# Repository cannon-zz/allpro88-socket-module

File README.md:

# KiCad Model of Logical Devices' ALLPRO88 PLCC Socket Module

## Overview

This provides a KiCad [schematic](https://github.com/user-attachments/files/24761395/socket_module_plcc_schematic.pdf) of the PLCC socket module for use with Logic Devices' ALLPRO88 software-driven device programmer.  The service manual scans available on the internet are incomprehensible.  I believe the schematic is correct.  The PCB's size and the locations of the DIN connectors, 48 pin ZIF connector and decoupling capacitors and transistors all match the original.  All other part locations are approximate, the PCB has not been routed, and the footprints for the PLCC sockets are not correct.  The PLCC sockets here have the wrong hole pattern, and are mirrored with respect to the originals.  The original module used Yamaichi IC120 series sockets, the "dead bug" variants (for which the chips are inserted upside down).  See a datasheet for the correct hole patterns.  The objective is not to allow a PLCC socket module to be reproduced from this project, but to provide a starting point for making a custom socket module.

## Board Size

Measuring my PCB to the nearest 0.5 mm, the PCB is 25.70 cm x 20.45 cm.

If it's imperial, and we allow some +/- for the saw cut accuracy, it could be 10 1/8" x 8" (= 25.7175 cm x 20.32 cm).

I found a comment in the service manual that the PCB is 10.100" x 8.05x" (x is unreadable, could be 0, 6 or 8 maybe).  0.001" = 0.0254 mm, so I don't think it really matters if that digit is a 0 or an 8.  10.1" x 8.05" = 25.65 cm x 20.45 cm which is within 0.5 mm of my measurements.

## DIN Connector Placement

From the corner of the PCB closest to the 44 pin PLCC socket, I mesaure pin C32 of J1 to be 100.8 mm horizontally from that corner, and 67.2 mm vertically.  The two DIN connectors appear to be positioned with respect to each other on a 2.54 mm grid:  A1 to A1 is 18 * 2.54 mm = 45.72 mm.  The status LEDs and their resistors appear to be on a 2.54 mm grid, centred between the DIN connectors

I suggest plugging the DIN connectors into the base, then placing the PCB onto them and either tightening the screws to hold them in that position or soldering enough pins to secure them, then removing the PCB with the connectors to continue soldering.  That way they're guaranteed to be aligned with their sockets after being soldered into position.

## Signal Names

The scans available on the internet of the original schematic, both for the socket module and the programmer's mother board, are incomprehensible.  Also, there are several inconsistent channel numbering schemes in Logical Devices' original documentation.  So:  what's here is my own invention.  Make of it what you will.

 * GND:  system power supply return.
 * -8 V, -5 V, +5 V, +12V, VREF:  main system power supplies.
 * VADJ:  main programmable, high current, power supply.  All pin driver voltages are derived from this.
 * VSR, VTH, VPU, ILIN:  pin driver power supplies.
 * !SOCKETEN:  active-low device select line indicating that the address bus is in the range 0x0280 to 0x02ff inclusively.  This is a 128 byte window reserved for the socket module.  On the universal PLCC module, reading from any address in this range returns the socket module ID, while writing to addresses in this range control the registers used to switch the pin decoupling capacitors on and off.
 * \phi_{0}, \phi_{1}:  the two phases used for driving the TTL clock output modes of the pin drivers.  When they are active they are guaranteed to be 180 degrees out of phase, but they can become inactive and enter the same state.
 * !XFER:  active low line to clock the pin driver DACs
 * !RD, !WR:  active low read- and write-enable signals.
 * !LED_BUSY, LED_IDLE:  common collector drives for the busy (red) and idle (green) LEDs.
 * !RESET:  active low system reset.  On the PLCC module, resets the decoupling capacitor registers to 0 (capacitors disconnected).
 * !SELECT0 -- !SELECT4:  active low device select lines for the first 5 pin driver modules, corresponding to channels 0 through 39 inclusively.  The ALLPRO88 was preceded by an earlier product that had only 40 channels, and it was presumably thought to be handy to have these signals brought out to the socket module to avoid duplicating address decoding circuitry in the event that lots of complex pin driver circuitry was needed for some part.
 * A0 -- A9:  partial system address bus.  The system address bus is 12 bits, but only the low 10 are present on the socket module.  Together with !SOCKETEN, only A0--A6 are needed to address the 128 byte window reserved for the socket module.
 * D0 -- D7:  system data bus.
 * OUT0 -- OUT87:  the 88 pin driver inputs/outputs.
 * SPARE1:  unused signal line that connects to the socket module, all pin driver boards, and both analogue 1 and analogue 2.  There are two unused voltage DACs on analogue 2, and I think a sensible thing to do would be to jumper one of them to this in line, to provide an additional programmable voltage to the system.  For example, the fixed 5 V linear regulators that generate the "TTL" output voltage on the pin driver boards could be replaced with adjustable regulators programmed by this voltage, making it easier to support non- 5 V logic.

## PAL

The PAL device is a look-up table for chip select line decoding.  To (I assume) simplify trace routing, pin driver channels are connected to ZIF socket pins close to their location on the DIN connector, in groups of 8 with 4 on one side of the socket and 4 on the other, while decoupling capacitor transistor drivers are connected to transistors sequentially along each side of the socket.  Additionally, for (again I assume) historical reasons only the first 40 channels have sequential addresses, the final 8 are offset at slightly higher addresses.  Altogther, these conditions create a somewhat complex relationship between the numerical address on the address bus and which transistor on which FET chip should be turned on or off, which motivates the use of a programmable logic device.

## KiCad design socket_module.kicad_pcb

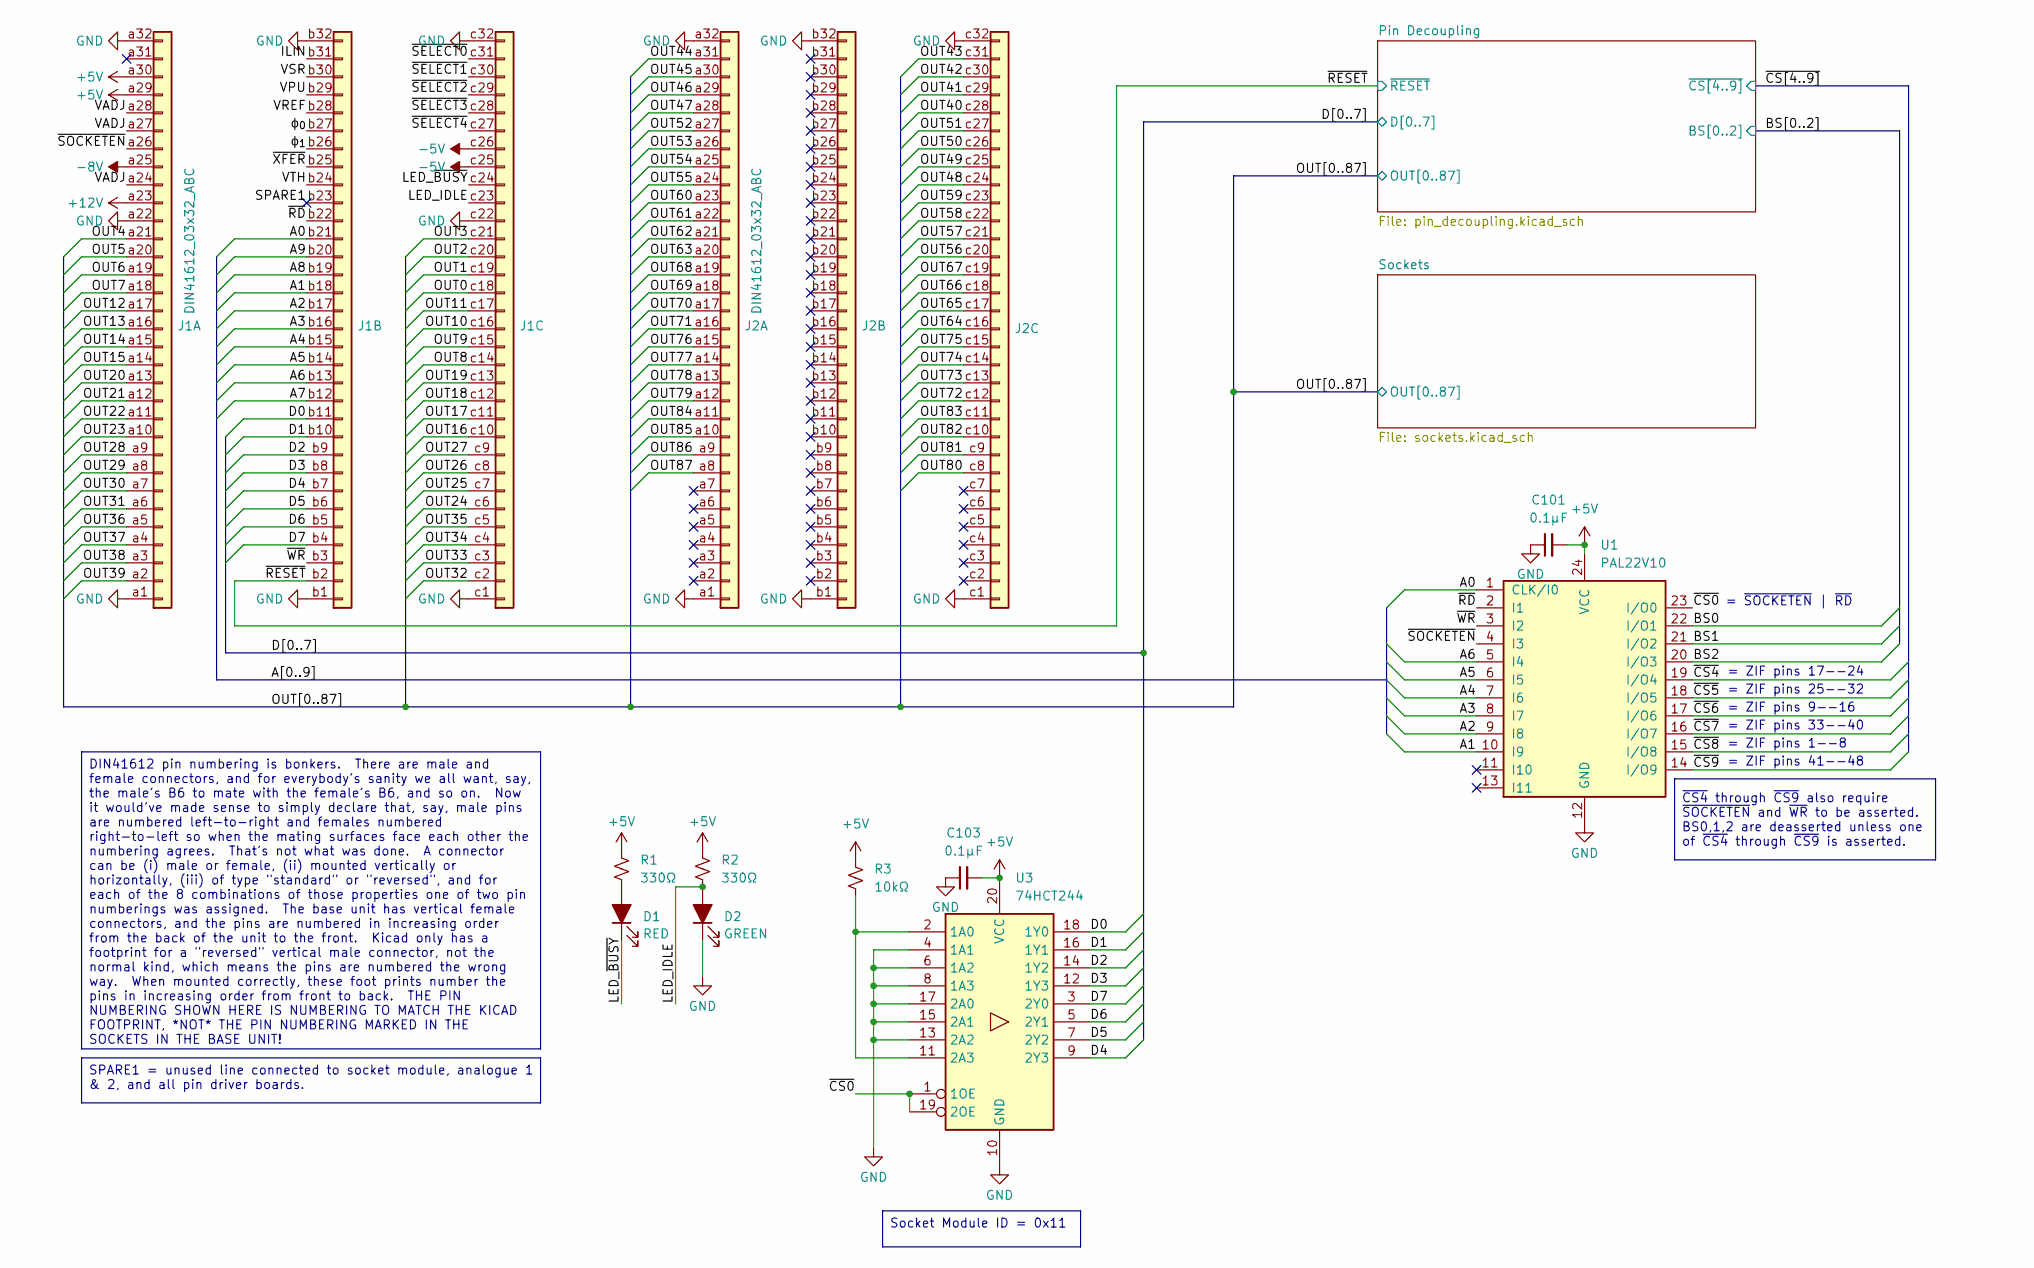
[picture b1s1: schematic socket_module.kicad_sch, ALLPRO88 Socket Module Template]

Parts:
C101, C103: 0.1μF; C_Disc_D7.5mm_W2.5mm_P5.00mm
D1: RED; LED_Rectangular_W5.0mm_H2.0mm
D2: GREEN; LED_Rectangular_W5.0mm_H2.0mm
J1, J2: DIN41612_03x32_ABC; DIN41612_R_3x32_Male_Vertical_THT
R1, R2: 330Ω; R_Axial_DIN0207_L6.3mm_D2.5mm_P10.16mm_Horizontal
R3: 10kΩ; R_Axial_DIN0207_L6.3mm_D2.5mm_P10.16mm_Horizontal
U1: PAL22V10; DIP-24_W7.62mm_Socket_LongPads
U3: 74HCT244; DIP-20_W7.62mm_LongPads

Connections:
+5V: C101.2, C103.2, J1.a29, J1.a30, R1.1, R2.1, R3.1, U1.24 (VCC), U3.20 (VCC); also elsewhere on the board
+12V: J1.a23
-5V: J1.c25, J1.c26
-8V: J1.a25
/A0: J1.b21, U1.1 (CLK/I0)
/A1: J1.b18, U1.10 (I9)
/A2: J1.b17, U1.9 (I8)
/A3: J1.b16, U1.8 (I7)
/A4: J1.b15, U1.7 (I6)
/A5: J1.b14, U1.6 (I5)
/A6: J1.b13, U1.5 (I4)
/A7: J1.b12
/A8: J1.b19
/A9: J1.b20
/BS0: U1.22 (I/O1); also elsewhere on the board
/BS1: U1.21 (I/O2); also elsewhere on the board
/BS2: U1.20 (I/O3); also elsewhere on the board
/D0: J1.b11, U3.18 (1Y0); also elsewhere on the board
/D1: J1.b10, U3.16 (1Y1)
/D2: J1.b9, U3.14 (1Y2)
/D3: J1.b8, U3.12 (1Y3)
/D4: J1.b7, U3.9 (2Y3)
/D5: J1.b6, U3.7 (2Y2)
/D6: J1.b5, U3.5 (2Y1)
/D7: J1.b4, U3.3 (2Y0)
/ILIN: J1.b31
/LED_IDLE: D2.2 (A), J1.c23, R2.2
/LED_~BUSY: D1.1 (K), J1.c24
/OUT0: J1.c18; also elsewhere on the board
/OUT1: J1.c19; also elsewhere on the board
/OUT2: J1.c20; also elsewhere on the board
/OUT3: J1.c21; also elsewhere on the board
/OUT4: J1.a21; also elsewhere on the board
/OUT5: J1.a20; also elsewhere on the board
/OUT6: J1.a19; also elsewhere on the board
/OUT7: J1.a18; also elsewhere on the board
/OUT8: J1.c14; also elsewhere on the board
/OUT9: J1.c15; also elsewhere on the board
/OUT10: J1.c16; also elsewhere on the board
/OUT11: J1.c17; also elsewhere on the board
/OUT12: J1.a17; also elsewhere on the board
/OUT13: J1.a16; also elsewhere on the board
/OUT14: J1.a15; also elsewhere on the board
/OUT15: J1.a14; also elsewhere on the board
/OUT16: J1.c10; also elsewhere on the board
/OUT17: J1.c11; also elsewhere on the board
/OUT18: J1.c12; also elsewhere on the board
/OUT19: J1.c13; also elsewhere on the board
/OUT20: J1.a13; also elsewhere on the board
/OUT21: J1.a12; also elsewhere on the board
/OUT22: J1.a11; also elsewhere on the board
/OUT23: J1.a10; also elsewhere on the board
/OUT24: J1.c6; also elsewhere on the board
/OUT25: J1.c7; also elsewhere on the board
/OUT26: J1.c8; also elsewhere on the board
/OUT27: J1.c9; also elsewhere on the board
/OUT28: J1.a9; also elsewhere on the board
/OUT29: J1.a8; also elsewhere on the board
/OUT30: J1.a7; also elsewhere on the board
/OUT31: J1.a6; also elsewhere on the board
/OUT32: J1.c2; also elsewhere on the board
/OUT33: J1.c3; also elsewhere on the board
/OUT34: J1.c4; also elsewhere on the board
/OUT35: J1.c5; also elsewhere on the board
/OUT36: J1.a5; also elsewhere on the board
/OUT37: J1.a4; also elsewhere on the board
/OUT38: J1.a3; also elsewhere on the board
/OUT39: J1.a2; also elsewhere on the board
/OUT40: J2.c28; also elsewhere on the board
/OUT41: J2.c29; also elsewhere on the board
/OUT42: J2.c30; also elsewhere on the board
/OUT43: J2.c31; also elsewhere on the board
/OUT44: J2.a31; also elsewhere on the board
/OUT45: J2.a30; also elsewhere on the board
/OUT46: J2.a29; also elsewhere on the board
/OUT47: J2.a28; also elsewhere on the board
/OUT48: J2.c24; also elsewhere on the board
/OUT49: J2.c25; also elsewhere on the board
/OUT50: J2.c26; also elsewhere on the board
/OUT51: J2.c27; also elsewhere on the board
/OUT52: J2.a27; also elsewhere on the board
/OUT53: J2.a26; also elsewhere on the board
/OUT54: J2.a25; also elsewhere on the board
/OUT55: J2.a24; also elsewhere on the board
/OUT56: J2.c20; also elsewhere on the board
/OUT57: J2.c21; also elsewhere on the board
/OUT58: J2.c22; also elsewhere on the board
/OUT59: J2.c23; also elsewhere on the board
/OUT60: J2.a23; also elsewhere on the board
/OUT61: J2.a22; also elsewhere on the board
/OUT62: J2.a21; also elsewhere on the board
/OUT63: J2.a20; also elsewhere on the board
/OUT64: J2.c16; also elsewhere on the board
/OUT65: J2.c17; also elsewhere on the board
/OUT66: J2.c18; also elsewhere on the board
/OUT67: J2.c19; also elsewhere on the board
/OUT68: J2.a19; also elsewhere on the board
/OUT69: J2.a18; also elsewhere on the board
/OUT70: J2.a17; also elsewhere on the board
/OUT71: J2.a16; also elsewhere on the board
/OUT72: J2.c12; also elsewhere on the board
/OUT73: J2.c13; also elsewhere on the board
/OUT74: J2.c14; also elsewhere on the board
/OUT75: J2.c15; also elsewhere on the board
/OUT76: J2.a15; also elsewhere on the board
/OUT77: J2.a14; also elsewhere on the board
/OUT78: J2.a13; also elsewhere on the board
/OUT79: J2.a12; also elsewhere on the board
/OUT80: J2.c8
/OUT81: J2.c9
/OUT82: J2.c10; also elsewhere on the board
/OUT83: J2.c11; also elsewhere on the board
/OUT84: J2.a11; also elsewhere on the board
/OUT85: J2.a10; also elsewhere on the board
/OUT86: J2.a9
/OUT87: J2.a8
/SPARE1: J1.b23
/VADJ: J1.a24, J1.a27, J1.a28
/VPU: J1.b29
/VREF: J1.b28
/VSR: J1.b30
/VTH: J1.b24 (Pin_a24)
/~CS0: U1.23 (I/O0), U3.1 (1OE), U3.19 (2OE)
/~CS4: U1.19 (I/O4); also elsewhere on the board
/~CS5: U1.18 (I/O5); also elsewhere on the board
/~CS6: U1.17 (I/O6); also elsewhere on the board
/~CS7: U1.16 (I/O7); also elsewhere on the board
/~CS8: U1.15 (I/O8); also elsewhere on the board
/~CS9: U1.14 (I/O9); also elsewhere on the board
/~RD: J1.b22, U1.2 (I1)
/~RESET: J1.b2; also elsewhere on the board
/~SELECT0: J1.c31
/~SELECT1: J1.c30
/~SELECT2: J1.c29
/~SELECT3: J1.c28
/~SELECT4: J1.c27
/~SOCKETEN: J1.a26, U1.4 (I3)
/~WR: J1.b3, U1.3 (I2)
/~XFER: J1.b25
/ϕ_{0}: J1.b27
/ϕ_{1}: J1.b26
GND: C101.1, C103.1, D2.1 (K), J1.a1, J1.a22, J1.a32, J1.b1, J1.b32, J1.c1, J1.c22, J1.c32, J2.a1, J2.a32, J2.b1, J2.b32, J2.c1, J2.c32, U1.12 (GND), U3.4 (1A1), U3.6 (1A2), U3.8 (1A3), U3.10 (GND), U3.13 (2A2), U3.15 (2A1), U3.17 (2A0); also elsewhere on the board
unnamed: D1.2 (A), R1.2
unnamed: R3.2, U3.2 (1A0), U3.11 (2A3)

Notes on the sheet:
= ZIF pins 33--40
= ~{SOCKETEN} | ~{RD}
= ZIF pins 17--24
= ZIF pins 41--48
= ZIF pins 1--8
= ZIF pins 25--32
= ZIF pins 9--16
~{CS4} through ~{CS9} also require ~{SOCKETEN} and ~{WR} to be asserted. BS0,1,2 are deasserted unless one of ~{CS4} through ~{CS9} is asserted.
Socket Module ID = 0x11
DIN41612 pin numbering is bonkers. There are male and female connectors, and for everybody's sanity we all want, say, the male's B6 to mate with the female's B6, and so on. Now it would've made sense to simply declare that, say, male pins are numbered left-to-right and females numbered right-to-lef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
SPARE1 = unused line connected to socket module, analogue 1 & 2, and all pin driver boards.

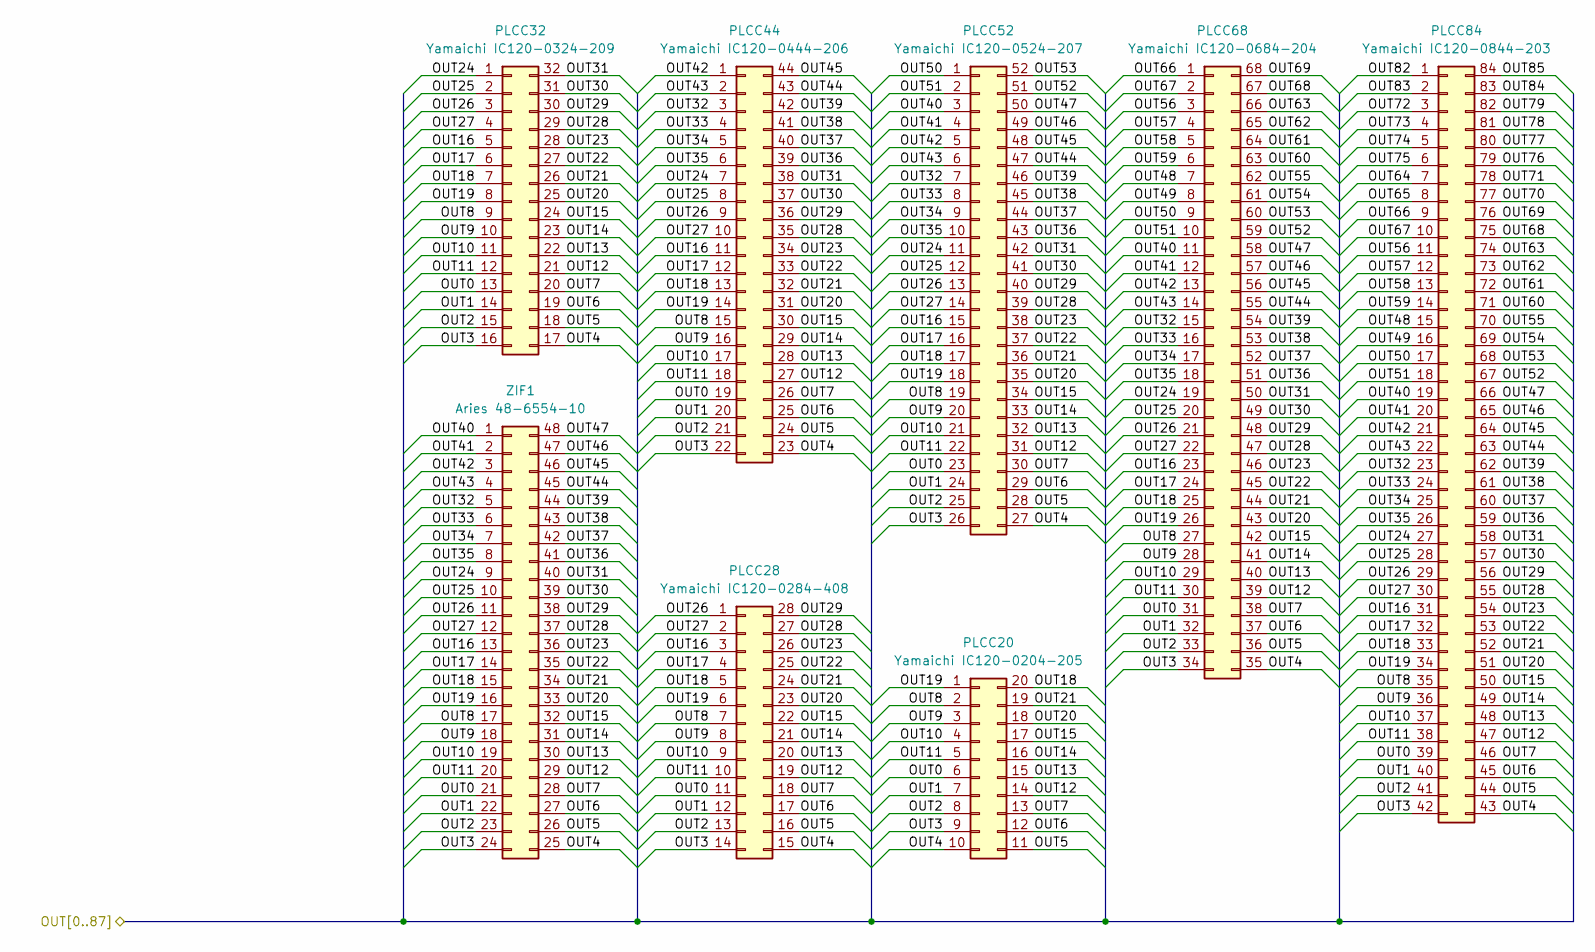
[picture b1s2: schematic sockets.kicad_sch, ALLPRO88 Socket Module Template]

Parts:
PLCC20: Yamaichi IC120-0204-205; PLCC-20_THT-Socket
PLCC28: Yamaichi IC120-0284-408; PLCC-28_THT-Socket
PLCC32: Yamaichi IC120-0324-209; PLCC-32_THT-Socket
PLCC44: Yamaichi IC120-0444-206; PLCC-44_THT-Socket
PLCC52: Yamaichi IC120-0524-207; PLCC-52_THT-Socket
PLCC68: Yamaichi IC120-0684-204; PLCC-68_THT-Socket
PLCC84: Yamaichi IC120-0844-203; PLCC-84_THT-Socket
ZIF1: Aries 48-6554-10; DIP-48_W15.24mm_Socket_LongPads

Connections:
/OUT0: PLCC20.6, PLCC28.11, PLCC32.13, PLCC44.19, PLCC52.23, PLCC68.31, PLCC84.39, ZIF1.21; also elsewhere on the board
/OUT1: PLCC20.7, PLCC28.12, PLCC32.14, PLCC44.20, PLCC52.24, PLCC68.32, PLCC84.40, ZIF1.22; also elsewhere on the board
/OUT2: PLCC20.8, PLCC28.13, PLCC32.15, PLCC44.21, PLCC52.25, PLCC68.33, PLCC84.41, ZIF1.23; also elsewhere on the board
/OUT3: PLCC20.9, PLCC28.14, PLCC32.16, PLCC44.22, PLCC52.26, PLCC68.34, PLCC84.42, ZIF1.24; also elsewhere on the board
/OUT4: PLCC20.10, PLCC28.15, PLCC32.17, PLCC44.23, PLCC52.27, PLCC68.35, PLCC84.43, ZIF1.25; also elsewhere on the board
/OUT5: PLCC20.11, PLCC28.16, PLCC32.18, PLCC44.24, PLCC52.28, PLCC68.36, PLCC84.44, ZIF1.26; also elsewhere on the board
/OUT6: PLCC20.12, PLCC28.17, PLCC32.19, PLCC44.25, PLCC52.29, PLCC68.37, PLCC84.45, ZIF1.27; also elsewhere on the board
/OUT7: PLCC20.13, PLCC28.18, PLCC32.20, PLCC44.26, PLCC52.30, PLCC68.38, PLCC84.46, ZIF1.28; also elsewhere on the board
/OUT8: PLCC20.2, PLCC28.7, PLCC32.9, PLCC44.15, PLCC52.19, PLCC68.27, PLCC84.35, ZIF1.17; also elsewhere on the board
/OUT9: PLCC20.3, PLCC28.8, PLCC32.10, PLCC44.16, PLCC52.20, PLCC68.28, PLCC84.36, ZIF1.18; also elsewhere on the board
/OUT10: PLCC20.4, PLCC28.9, PLCC32.11, PLCC44.17, PLCC52.21, PLCC68.29, PLCC84.37, ZIF1.19; also elsewhere on the board
/OUT11: PLCC20.5, PLCC28.10, PLCC32.12, PLCC44.18, PLCC52.22, PLCC68.30, PLCC84.38, ZIF1.20; also elsewhere on the board
/OUT12: PLCC20.14, PLCC28.19, PLCC32.21, PLCC44.27, PLCC52.31, PLCC68.39, PLCC84.47, ZIF1.29; also elsewhere on the board
/OUT13: PLCC20.15, PLCC28.20, PLCC32.22, PLCC44.28, PLCC52.32, PLCC68.40, PLCC84.48, ZIF1.30; also elsewhere on the board
/OUT14: PLCC20.16, PLCC28.21, PLCC32.23, PLCC44.29, PLCC52.33, PLCC68.41, PLCC84.49, ZIF1.31; also elsewhere on the board
/OUT15: PLCC20.17, PLCC28.22, PLCC32.24, PLCC44.30, PLCC52.34, PLCC68.42, PLCC84.50, ZIF1.32; also elsewhere on the board
/OUT16: PLCC28.3, PLCC32.5, PLCC44.11, PLCC52.15, PLCC68.23, PLCC84.31, ZIF1.13; also elsewhere on the board
/OUT17: PLCC28.4, PLCC32.6, PLCC44.12, PLCC52.16, PLCC68.24, PLCC84.32, ZIF1.14; also elsewhere on the board
/OUT18: PLCC20.20, PLCC28.5, PLCC32.7, PLCC44.13, PLCC52.17, PLCC68.25, PLCC84.33, ZIF1.15; also elsewhere on the board
/OUT19: PLCC20.1, PLCC28.6, PLCC32.8, PLCC44.14, PLCC52.18, PLCC68.26, PLCC84.34, ZIF1.16; also elsewhere on the board
/OUT20: PLCC20.18, PLCC28.23, PLCC32.25, PLCC44.31, PLCC52.35, PLCC68.43, PLCC84.51, ZIF1.33; also elsewhere on the board
/OUT21: PLCC20.19, PLCC28.24, PLCC32.26, PLCC44.32, PLCC52.36, PLCC68.44, PLCC84.52, ZIF1.34; also elsewhere on the board
/OUT22: PLCC28.25, PLCC32.27, PLCC44.33, PLCC52.37, PLCC68.45, PLCC84.53, ZIF1.35; also elsewhere on the board
/OUT23: PLCC28.26, PLCC32.28, PLCC44.34, PLCC52.38, PLCC68.46, PLCC84.54, ZIF1.36; also elsewhere on the board
/OUT24: PLCC32.1, PLCC44.7, PLCC52.11, PLCC68.19, PLCC84.27, ZIF1.9; also elsewhere on the board
/OUT25: PLCC32.2, PLCC44.8, PLCC52.12, PLCC68.20, PLCC84.28, ZIF1.10; also elsewhere on the board
/OUT26: PLCC28.1, PLCC32.3, PLCC44.9, PLCC52.13, PLCC68.21, PLCC84.29, ZIF1.11; also elsewhere on the board
/OUT27: PLCC28.2, PLCC32.4, PLCC44.10, PLCC52.14, PLCC68.22, PLCC84.30, ZIF1.12; also elsewhere on the board
/OUT28: PLCC28.27, PLCC32.29, PLCC44.35, PLCC52.39, PLCC68.47, PLCC84.55, ZIF1.37; also elsewhere on the board
/OUT29: PLCC28.28, PLCC32.30, PLCC44.36, PLCC52.40, PLCC68.48, PLCC84.56, ZIF1.38; also elsewhere on the board
/OUT30: PLCC32.31, PLCC44.37, PLCC52.41, PLCC68.49, PLCC84.57, ZIF1.39; also elsewhere on the board
/OUT31: PLCC32.32, PLCC44.38, PLCC52.42, PLCC68.50, PLCC84.58, ZIF1.40; also elsewhere on the board
/OUT32: PLCC44.3, PLCC52.7, PLCC68.15, PLCC84.23, ZIF1.5; also elsewhere on the board
/OUT33: PLCC44.4, PLCC52.8, PLCC68.16, PLCC84.24, ZIF1.6; also elsewhere on the board
/OUT34: PLCC44.5, PLCC52.9, PLCC68.17, PLCC84.25, ZIF1.7; also elsewhere on the board
/OUT35: PLCC44.6, PLCC52.10, PLCC68.18, PLCC84.26, ZIF1.8; also elsewhere on the board
/OUT36: PLCC44.39, PLCC52.43, PLCC68.51, PLCC84.59, ZIF1.41; also elsewhere on the board
/OUT37: PLCC44.40, PLCC52.44, PLCC68.52, PLCC84.60, ZIF1.42; also elsewhere on the board
/OUT38: PLCC44.41, PLCC52.45, PLCC68.53, PLCC84.61, ZIF1.43; also elsewhere on the board
/OUT39: PLCC44.42, PLCC52.46, PLCC68.54, PLCC84.62, ZIF1.44; also elsewhere on the board
/OUT40: PLCC52.3, PLCC68.11, PLCC84.19, ZIF1.1; also elsewhere on the board
/OUT41: PLCC52.4, PLCC68.12, PLCC84.20, ZIF1.2; also elsewhere on the board
/OUT42: PLCC44.1, PLCC52.5, PLCC68.13, PLCC84.21, ZIF1.3; also elsewhere on the board
/OUT43: PLCC44.2, PLCC52.6, PLCC68.14, PLCC84.22, ZIF1.4; also elsewhere on the board
/OUT44: PLCC44.43, PLCC52.47, PLCC68.55, PLCC84.63, ZIF1.45; also elsewhere on the board
/OUT45: PLCC44.44, PLCC52.48, PLCC68.56, PLCC84.64, ZIF1.46; also elsewhere on the board
/OUT46: PLCC52.49, PLCC68.57, PLCC84.65, ZIF1.47; also elsewhere on the board
/OUT47: PLCC52.50, PLCC68.58, PLCC84.66, ZIF1.48; also elsewhere on the board
/OUT48: PLCC68.7, PLCC84.15; also elsewhere on the board
/OUT49: PLCC68.8, PLCC84.16; also elsewhere on the board
/OUT50: PLCC52.1, PLCC68.9, PLCC84.17; also elsewhere on the board
/OUT51: PLCC52.2, PLCC68.10, PLCC84.18; also elsewhere on the board
/OUT52: PLCC52.51, PLCC68.59, PLCC84.67; also elsewhere on the board
/OUT53: PLCC52.52, PLCC68.60, PLCC84.68; also elsewhere on the board
/OUT54: PLCC68.61, PLCC84.69; also elsewhere on the board
/OUT55: PLCC68.62, PLCC84.70; also elsewhere on the board
/OUT56: PLCC68.3, PLCC84.11; also elsewhere on the board
/OUT57: PLCC68.4, PLCC84.12; also elsewhere on the board
/OUT58: PLCC68.5, PLCC84.13; also elsewhere on the board
/OUT59: PLCC68.6, PLCC84.14; also elsewhere on the board
/OUT60: PLCC68.63, PLCC84.71; also elsewhere on the board
/OUT61: PLCC68.64, PLCC84.72; also elsewhere on the board
/OUT62: PLCC68.65, PLCC84.73; also elsewhere on the board
/OUT63: PLCC68.66, PLCC84.74; also elsewhere on the board
/OUT64: PLCC84.7; also elsewhere on the board
/OUT65: PLCC84.8; also elsewhere on the board
/OUT66: PLCC68.1, PLCC84.9; also elsewhere on the board
/OUT67: PLCC68.2, PLCC84.10; also elsewhere on the board
/OUT68: PLCC68.67, PLCC84.75; also elsewhere on the board
/OUT69: PLCC68.68, PLCC84.76; also elsewhere on the board
/OUT70: PLCC84.77; also elsewhere on the board
/OUT71: PLCC84.78; also elsewhere on the board
/OUT72: PLCC84.3; also elsewhere on the board
/OUT73: PLCC84.4; also elsewhere on the board
/OUT74: PLCC84.5; also elsewhere on the board
/OUT75: PLCC84.6; also elsewhere on the board
/OUT76: PLCC84.79; also elsewhere on the board
/OUT77: PLCC84.80; also elsewhere on the board
/OUT78: PLCC84.81; also elsewhere on the board
/OUT79: PLCC84.82; also elsewhere on the board
/OUT82: PLCC84.1; also elsewhere on the board
/OUT83: PLCC84.2; also elsewhere on the board
/OUT84: PLCC84.83; also elsewhere on the board
/OUT85: PLCC84.84; also elsewhere on the board

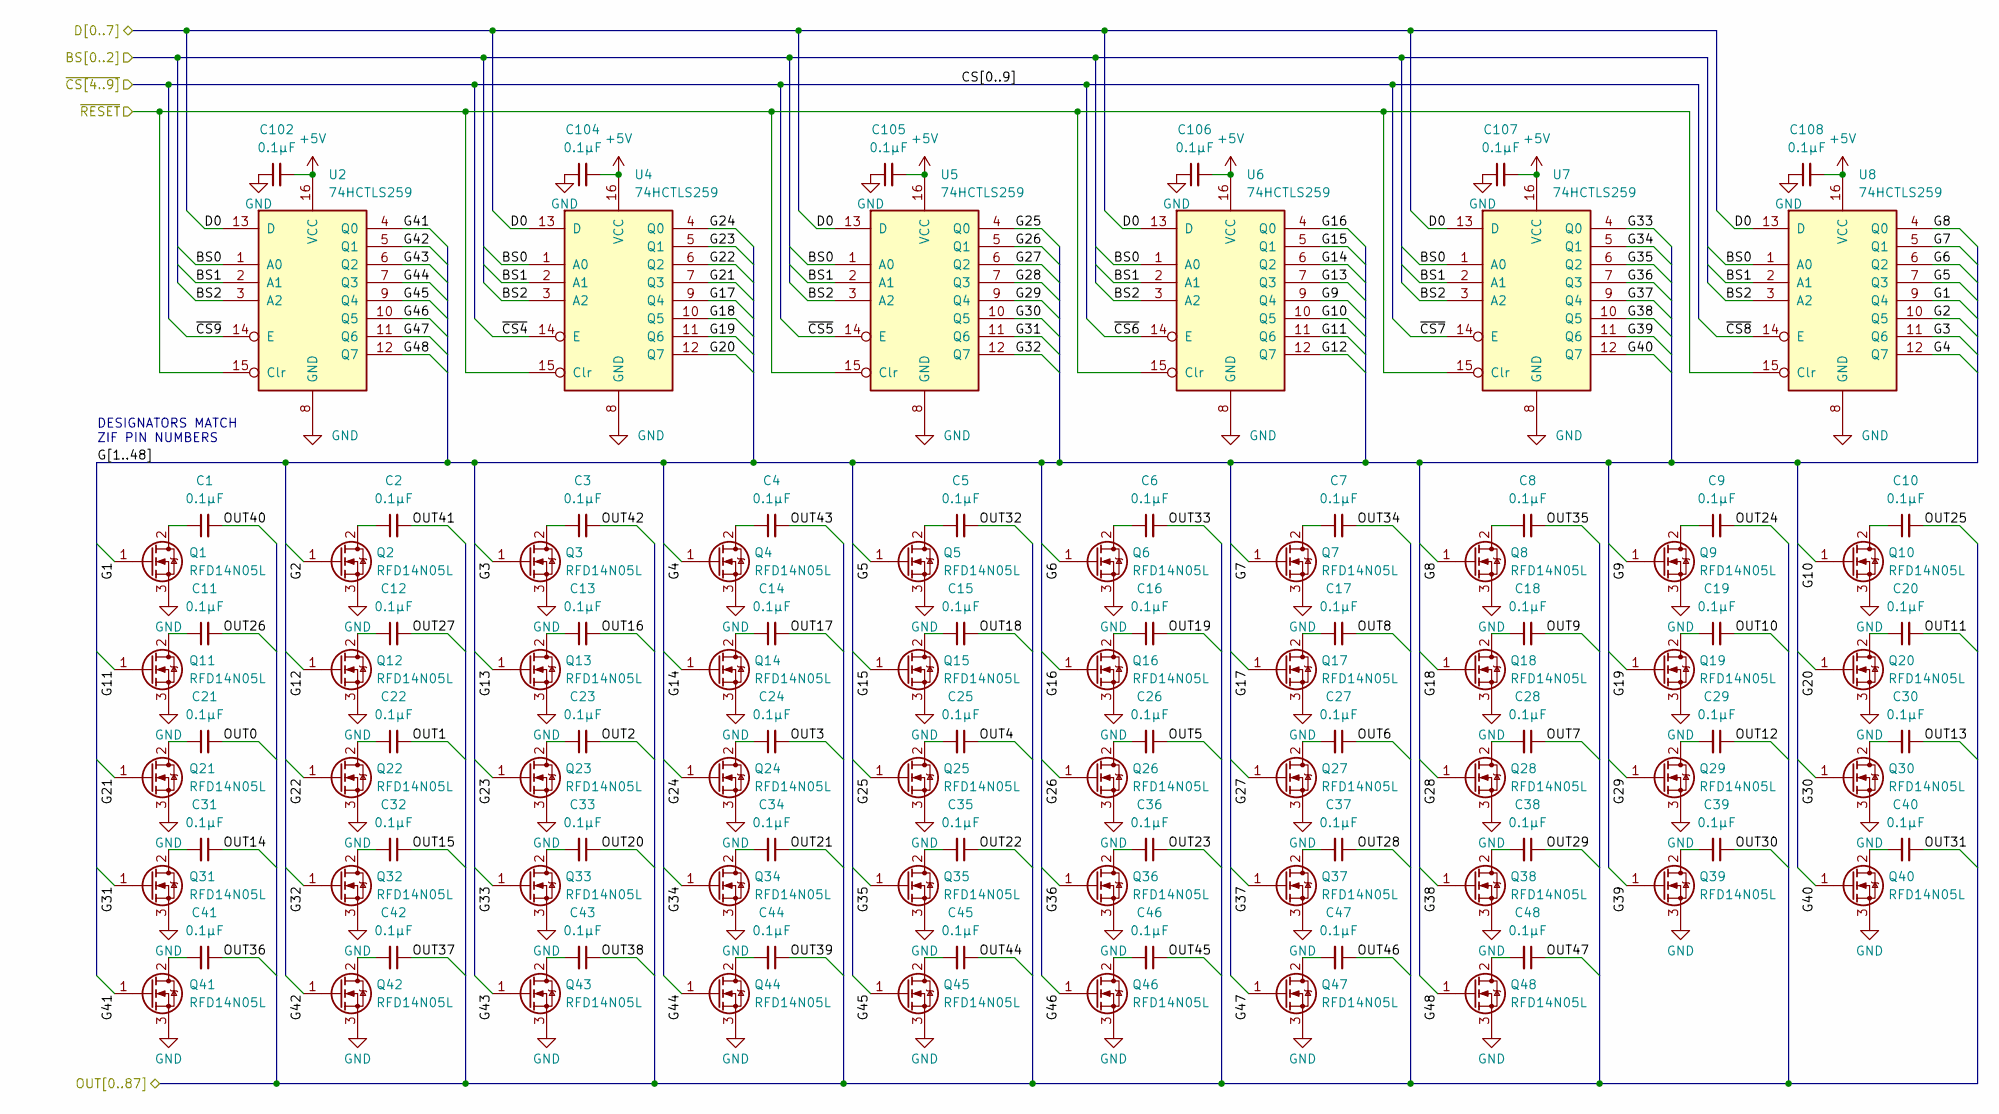
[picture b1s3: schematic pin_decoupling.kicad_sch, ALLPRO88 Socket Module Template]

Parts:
C1, C2, C3, C4, C5, C6, C7, C8, C9, C10, C11, C12, C13, C14, C15, C16, C17, C18, C19, C20, C21, C22, C23, C24, C25, C26, C27, C28, C29, C30, C31, C32, C33, C34, C35, C36, C37, C38, C39, C40, C41, C42, C43, C44, C45, C46, C47, C48, C102, C104, C105, C106, C107, C108: 0.1μF; C_Disc_D7.5mm_W2.5mm_P5.00mm
Q1, Q2, Q3, Q4, Q5, Q6, Q7, Q8, Q9, Q10, Q11, Q12, Q13, Q14, Q15, Q16, Q17, Q18, Q19, Q20, Q21, Q22, Q23, Q24, Q25, Q26, Q27, Q28, Q29, Q30, Q31, Q32, Q33, Q34, Q35, Q36, Q37, Q38, Q39, Q40, Q41, Q42, Q43, Q44, Q45, Q46, Q47, Q48: RFD14N05L; TO-251-3_Vertical
U2, U4, U5, U6, U7, U8: 74HCTLS259; DIP-16_W7.62mm_LongPads

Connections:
+5V: C102.2, C104.2, C105.2, C106.2, C107.2, C108.2, U2.16 (VCC), U4.16 (VCC), U5.16 (VCC), U6.16 (VCC), U7.16 (VCC), U8.16 (VCC); also elsewhere on the board
/BS0: U2.1 (A0), U4.1 (A0), U5.1 (A0), U6.1 (A0), U7.1 (A0), U8.1 (A0); also elsewhere on the board
/BS1: U2.2 (A1), U4.2 (A1), U5.2 (A1), U6.2 (A1), U7.2 (A1), U8.2 (A1); also elsewhere on the board
/BS2: U2.3 (A2), U4.3 (A2), U5.3 (A2), U6.3 (A2), U7.3 (A2), U8.3 (A2); also elsewhere on the board
/D0: U2.13 (D), U4.13 (D), U5.13 (D), U6.13 (D), U7.13 (D), U8.13 (D); also elsewhere on the board
/OUT0: C21.2; also elsewhere on the board
/OUT1: C22.2; also elsewhere on the board
/OUT2: C23.2; also elsewhere on the board
/OUT3: C24.2; also elsewhere on the board
/OUT4: C25.1; also elsewhere on the board
/OUT5: C26.1; also elsewhere on the board
/OUT6: C27.1; also elsewhere on the board
/OUT7: C28.1; also elsewhere on the board
/OUT8: C17.2; also elsewhere on the board
/OUT9: C18.2; also elsewhere on the board
/OUT10: C19.2; also elsewhere on the board
/OUT11: C20.2; also elsewhere on the board
/OUT12: C29.1; also elsewhere on the board
/OUT13: C30.1; also elsewhere on the board
/OUT14: C31.1; also elsewhere on the board
/OUT15: C32.1; also elsewhere on the board
/OUT16: C13.2; also elsewhere on the board
/OUT17: C14.2; also elsewhere on the board
/OUT18: C15.2; also elsewhere on the board
/OUT19: C16.2; also elsewhere on the board
/OUT20: C33.1; also elsewhere on the board
/OUT21: C34.1; also elsewhere on the board
/OUT22: C35.1; also elsewhere on the board
/OUT23: C36.1; also elsewhere on the board
/OUT24: C9.2; also elsewhere on the board
/OUT25: C10.2; also elsewhere on the board
/OUT26: C11.2; also elsewhere on the board
/OUT27: C12.2; also elsewhere on the board
/OUT28: C37.1; also elsewhere on the board
/OUT29: C38.1; also elsewhere on the board
/OUT30: C39.1; also elsewhere on the board
/OUT31: C40.1; also elsewhere on the board
/OUT32: C5.2; also elsewhere on the board
/OUT33: C6.2; also elsewhere on the board
/OUT34: C7.2; also elsewhere on the board
/OUT35: C8.2; also elsewhere on the board
/OUT36: C41.1; also elsewhere on the board
/OUT37: C42.1; also elsewhere on the board
/OUT38: C43.1; also elsewhere on the board
/OUT39: C44.1; also elsewhere on the board
/OUT40: C1.2; also elsewhere on the board
/OUT41: C2.2; also elsewhere on the board
/OUT42: C3.2; also elsewhere on the board
/OUT43: C4.2; also elsewhere on the board
/OUT44: C45.1; also elsewhere on the board
/OUT45: C46.1; also elsewhere on the board
/OUT46: C47.1; also elsewhere on the board
/OUT47: C48.1; also elsewhere on the board
/Pin Decoupling/G1: Q1.1 (G), U8.9 (Q4)
/Pin Decoupling/G2: Q2.1 (G), U8.10 (Q5)
/Pin Decoupling/G3: Q3.1 (G), U8.11 (Q6)
/Pin Decoupling/G4: Q4.1 (G), U8.12 (Q7)
/Pin Decoupling/G5: Q5.1 (G), U8.7 (Q3)
/Pin Decoupling/G6: Q6.1 (G), U8.6 (Q2)
/Pin Decoupling/G7: Q7.1 (G), U8.5 (Q1)
/Pin Decoupling/G8: Q8.1 (G), U8.4 (Q0)
/Pin Decoupling/G9: Q9.1 (G), U6.9 (Q4)
/Pin Decoupling/G10: Q10.1 (G), U6.10 (Q5)
/Pin Decoupling/G11: Q11.1 (G), U6.11 (Q6)
/Pin Decoupling/G12: Q12.1 (G), U6.12 (Q7)
/Pin Decoupling/G13: Q13.1 (G), U6.7 (Q3)
/Pin Decoupling/G14: Q14.1 (G), U6.6 (Q2)
/Pin Decoupling/G15: Q15.1 (G), U6.5 (Q1)
/Pin Decoupling/G16: Q16.1 (G), U6.4 (Q0)
/Pin Decoupling/G17: Q17.1 (G), U4.9 (Q4)
/Pin Decoupling/G18: Q18.1 (G), U4.10 (Q5)
/Pin Decoupling/G19: Q19.1 (G), U4.11 (Q6)
/Pin Decoupling/G20: Q20.1 (G), U4.12 (Q7)
/Pin Decoupling/G21: Q21.1 (G), U4.7 (Q3)
/Pin Decoupling/G22: Q22.1 (G), U4.6 (Q2)
/Pin Decoupling/G23: Q23.1 (G), U4.5 (Q1)
/Pin Decoupling/G24: Q24.1 (G), U4.4 (Q0)
/Pin Decoupling/G25: Q25.1 (G), U5.4 (Q0)
/Pin Decoupling/G26: Q26.1 (G), U5.5 (Q1)
/Pin Decoupling/G27: Q27.1 (G), U5.6 (Q2)
/Pin Decoupling/G28: Q28.1 (G), U5.7 (Q3)
/Pin Decoupling/G29: Q29.1 (G), U5.9 (Q4)
/Pin Decoupling/G30: Q30.1 (G), U5.10 (Q5)
/Pin Decoupling/G31: Q31.1 (G), U5.11 (Q6)
/Pin Decoupling/G32: Q32.1 (G), U5.12 (Q7)
/Pin Decoupling/G33: Q33.1 (G), U7.4 (Q0)
/Pin Decoupling/G34: Q34.1 (G), U7.5 (Q1)
/Pin Decoupling/G35: Q35.1 (G), U7.6 (Q2)
/Pin Decoupling/G36: Q36.1 (G), U7.7 (Q3)
/Pin Decoupling/G37: Q37.1 (G), U7.9 (Q4)
/Pin Decoupling/G38: Q38.1 (G), U7.10 (Q5)
/Pin Decoupling/G39: Q39.1 (G), U7.11 (Q6)
/Pin Decoupling/G40: Q40.1 (G), U7.12 (Q7)
/Pin Decoupling/G41: Q41.1 (G), U2.4 (Q0)
/Pin Decoupling/G42: Q42.1 (G), U2.5 (Q1)
/Pin Decoupling/G43: Q43.1 (G), U2.6 (Q2)
/Pin Decoupling/G44: Q44.1 (G), U2.7 (Q3)
/Pin Decoupling/G45: Q45.1 (G), U2.9 (Q4)
/Pin Decoupling/G46: Q46.1 (G), U2.10 (Q5)
/Pin Decoupling/G47: Q47.1 (G), U2.11 (Q6)
/Pin Decoupling/G48: Q48.1 (G), U2.12 (Q7)
/~CS4: U4.14 (E); also elsewhere on the board
/~CS5: U5.14 (E); also elsewhere on the board
/~CS6: U6.14 (E); also elsewhere on the board
/~CS7: U7.14 (E); also elsewhere on the board
/~CS8: U8.14 (E); also elsewhere on the board
/~CS9: U2.14 (E); also elsewhere on the board
/~RESET: U2.15 (Clr), U4.15 (Clr), U5.15 (Clr), U6.15 (Clr), U7.15 (Clr), U8.15 (Clr); also elsewhere on the board
GND: C102.1, C104.1, C105.1, C106.1, C107.1, C108.1, Q1.3 (S), Q2.3 (S), Q3.3 (S), Q4.3 (S), Q5.3 (S), Q6.3 (S), Q7.3 (S), Q8.3 (S), Q9.3 (S), Q10.3 (S), Q11.3 (S), Q12.3 (S), Q13.3 (S), Q14.3 (S), Q15.3 (S), Q16.3 (S), Q17.3 (S), Q18.3 (S), Q19.3 (S), Q20.3 (S), Q21.3 (S), Q22.3 (S), Q23.3 (S), Q24.3 (S), Q25.3 (S), Q26.3 (S), Q27.3 (S), Q28.3 (S), Q29.3 (S), Q30.3 (S), Q31.3 (S), Q32.3 (S), Q33.3 (S), Q34.3 (S), Q35.3 (S), Q36.3 (S), Q37.3 (S), Q38.3 (S), Q39.3 (S), Q40.3 (S), Q41.3 (S), Q42.3 (S), Q43.3 (S), Q44.3 (S), Q45.3 (S), Q46.3 (S), Q47.3 (S), Q48.3 (S), U2.8 (GND), U4.8 (GND), U5.8 (GND), U6.8 (GND), U7.8 (GND), U8.8 (GND); also elsewhere on the board
unnamed: C1.1, Q1.2 (D)
unnamed: C2.1, Q2.2 (D)
unnamed: C3.1, Q3.2 (D)
unnamed: C4.1, Q4.2 (D)
unnamed: C5.1, Q5.2 (D)
unnamed: C6.1, Q6.2 (D)
unnamed: C7.1, Q7.2 (D)
unnamed: C8.1, Q8.2 (D)
unnamed: C9.1, Q9.2 (D)
unnamed: C10.1, Q10.2 (D)
unnamed: C11.1, Q11.2 (D)
unnamed: C12.1, Q12.2 (D)
unnamed: C13.1, Q13.2 (D)
unnamed: C14.1, Q14.2 (D)
unnamed: C15.1, Q15.2 (D)
unnamed: C16.1, Q16.2 (D)
unnamed: C17.1, Q17.2 (D)
unnamed: C18.1, Q18.2 (D)
unnamed: C19.1, Q19.2 (D)
unnamed: C20.1, Q20.2 (D)
unnamed: C21.1, Q21.2 (D)
unnamed: C22.1, Q22.2 (D)
unnamed: C23.1, Q23.2 (D)
unnamed: C24.1, Q24.2 (D)
unnamed: C25.2, Q25.2 (D)
unnamed: C26.2, Q26.2 (D)
unnamed: C27.2, Q27.2 (D)
unnamed: C28.2, Q28.2 (D)
unnamed: C29.2, Q29.2 (D)
unnamed: C30.2, Q30.2 (D)
unnamed: C31.2, Q31.2 (D)
unnamed: C32.2, Q32.2 (D)
unnamed: C33.2, Q33.2 (D)
unnamed: C34.2, Q34.2 (D)
unnamed: C35.2, Q35.2 (D)
unnamed: C36.2, Q36.2 (D)
unnamed: C37.2, Q37.2 (D)
unnamed: C38.2, Q38.2 (D)
unnamed: C39.2, Q39.2 (D)
unnamed: C40.2, Q40.2 (D)
unnamed: C41.2, Q41.2 (D)
unnamed: C42.2, Q42.2 (D)
unnamed: C43.2, Q43.2 (D)
unnamed: C44.2, Q44.2 (D)
unnamed: C45.2, Q45.2 (D)
unnamed: C46.2, Q46.2 (D)
unnamed: C47.2, Q47.2 (D)
unnamed: C48.2, Q48.2 (D)

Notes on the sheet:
DESIGNATORS MATCH ZIF PIN NUMBERS

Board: 2 copper layers, 127 parts (10 on the bottom side), 217 nets, no tracks yet.

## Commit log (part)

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2025-05-29 original commit
    - the schematic should be exactly correct
    - the PCB size matches the PLCC socket module's PCB
    - the placement of the DIN connectors matches their locations on the PLCC socket module's PCB
    - the 48 pin ZIF socket is placed in the correct location WRT the DIN connectors
    - the decoupling capacitors and associated transistors are placed in the correct locations (except half of the transistors are rotated 180 degrees for convenience)
    - nothing else is positioned properly, it's just approximate, and there are no PCB traces.
2025-05-29 add README.md
2025-05-30 README.md
    - add comment about board dimensions.
2025-05-30 README.md
    - fix link to schematic
2025-05-30 README.md:
    - add a description of the signals on the sockets
2025-06-02 updates:
    - update symbols and footprints from library
    - re-correct 84 pin PLCC pin numbers
    - reset transistors to TO-2whatever from SMD
    - adjust position of DIN connectors, LEDs and their resistors (and 48 pin DIP and transistors and decoupling capacitors): measured again.
2025-06-02 add .gitignore
2026-01-11 decoded PAL contents, added notes
2026-01-21 update schematic PDF url
